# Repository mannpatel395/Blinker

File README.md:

# Blinker
Making 10 LEDs blink using 555 fundametal

## PCB:

Schematics:

PCB:

## 3D View:

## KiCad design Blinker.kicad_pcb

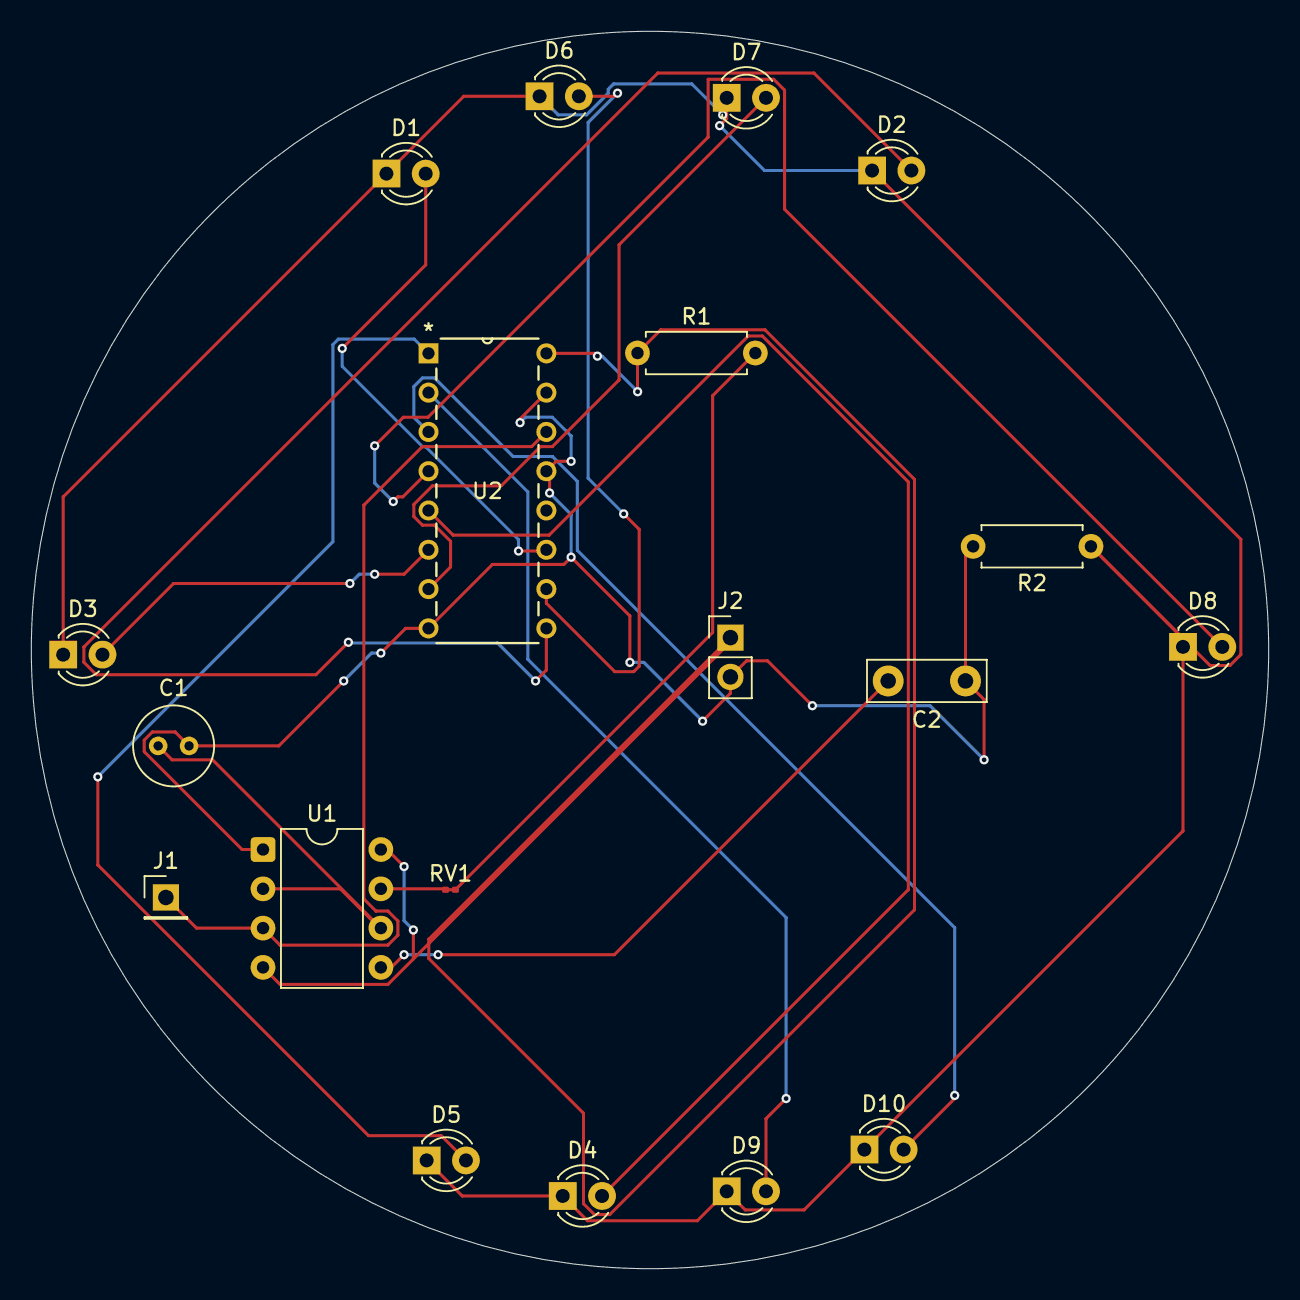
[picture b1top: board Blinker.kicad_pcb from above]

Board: 2 copper layers, 80.0 x 80.0 mm, 19 parts (0 on the bottom side), 17 nets.

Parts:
C1: 1uF; C_Radial_D5.0mm_H5.0mm_P2.00mm
C2: 0.01uF; C_Disc_D7.5mm_W2.5mm_P5.00mm
D1, D2, D3, D4, D5, D6, D7, D8, D9, D10: LED; LED_D3.0mm
J1: Conn_01x01_Socket; PinHeader_1x01_P2.54mm_Vertical
J2: Conn_01x02_Socket; PinHeader_1x02_P2.54mm_Vertical
R1: 1k; R_Axial_DIN0207_L6.3mm_D2.5mm_P7.62mm_Horizontal
R2: 470; R_Axial_DIN0207_L6.3mm_D2.5mm_P7.62mm_Horizontal
RV1: 50k; R_0201_0603Metric
U1: NE555P; DIP-8_W7.62mm
U2: 4017; N16

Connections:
+5V: J2.1, R1.1, U1.4 (~RST), U1.8 (VCC), U2.16 (VDD)
GND: C1.2, C2.1, J2.2, R2.2, U1.1 (GND), U2.8 (VSS), U2.13 (CKEN), U2.15 (Reset)
unnamed: D1.2 (A), U2.11 (Q9)
unnamed: D1.1 (K), D2.1 (K), D3.1 (K), D4.1 (K), D5.1 (K), D6.1 (K), D7.1 (K), D8.1 (K), D9.1 (K), D10.1 (K), R2.1
unnamed: D2.2 (A), U2.9 (Q8)
unnamed: D3.2 (A), U2.6 (Q7)
unnamed: D4.2 (A), U2.5 (Q6)
unnamed: D5.2 (A), U2.1 (Q5)
unnamed: D6.2 (A), U2.10 (Q4)
unnamed: D7.2 (A), U2.7 (Q3)
unnamed: D8.2 (A), U2.4 (Q2)
unnamed: D9.2 (A), U2.2 (Q1)
unnamed: D10.2 (A), U2.3 (Q0)
unnamed: C2.2, U1.5 (CONT)
unnamed: R1.2, RV1.1, RV1.2, U1.7 (DISCH)
OUT: J1.1, U1.3 (OUT), U2.14 (CLK)
TR: C1.1, U1.2 (TRIG), U1.6 (THRES)
